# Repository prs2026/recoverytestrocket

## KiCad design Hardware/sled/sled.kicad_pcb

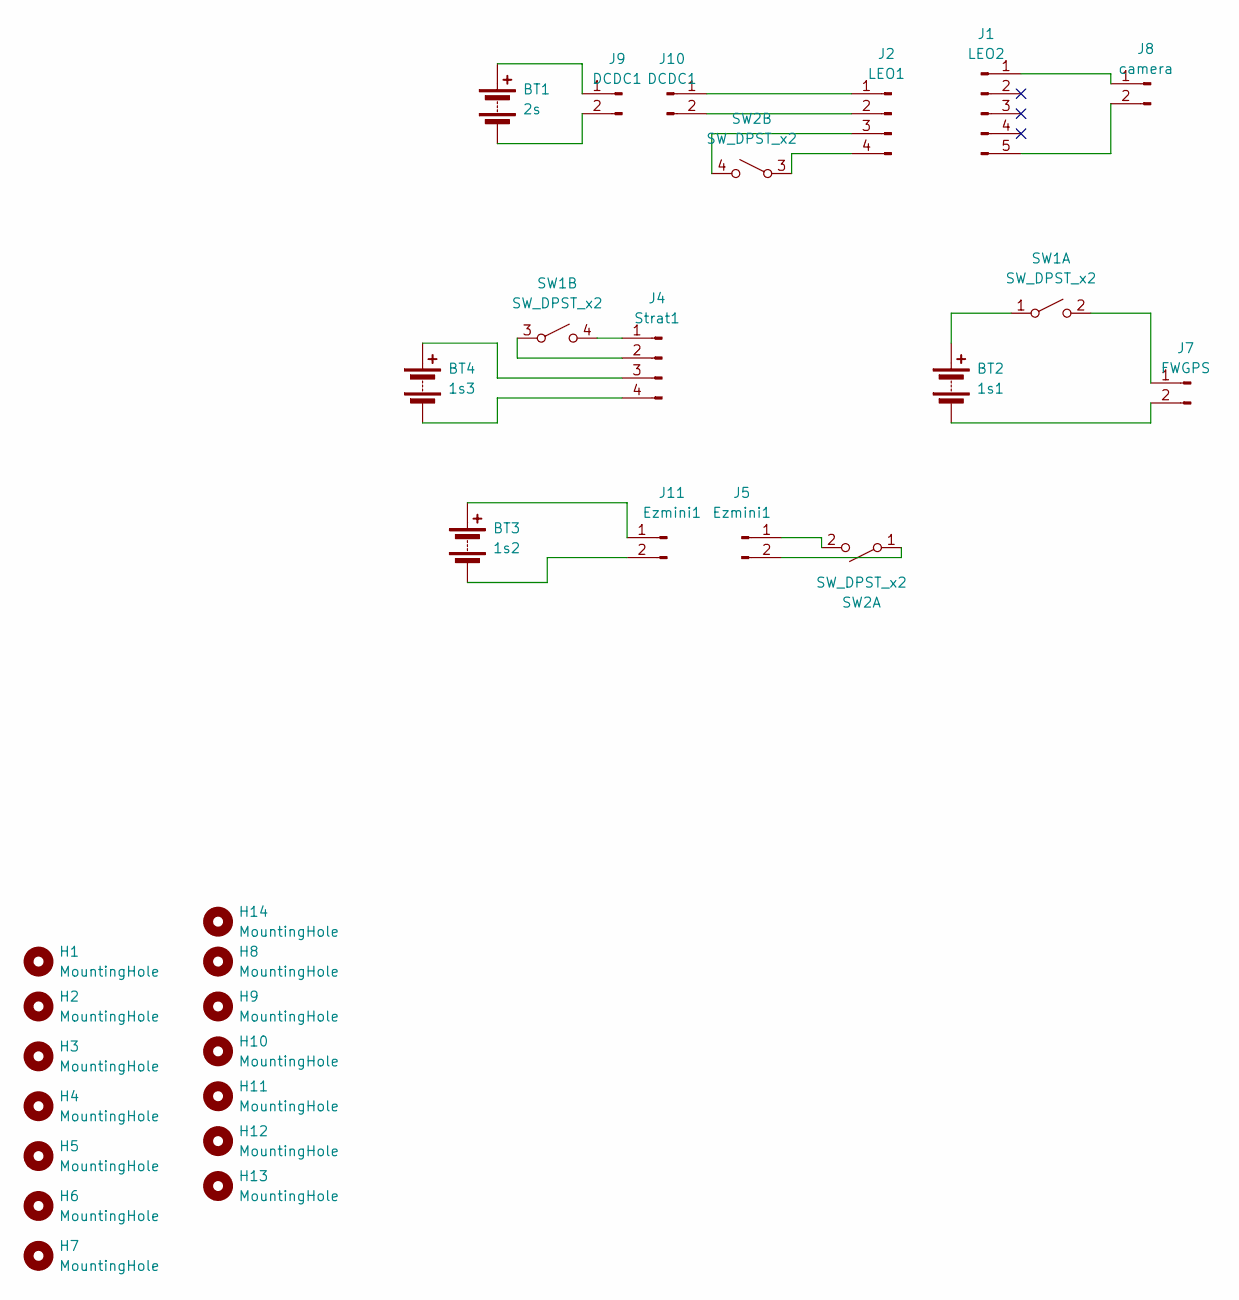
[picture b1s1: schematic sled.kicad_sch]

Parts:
BT1: 2s; PinHeader_1x02_P2.54mm_Vertical
BT2: 1s1; PinHeader_1x02_P2.54mm_Vertical
BT3: 1s2; PinHeader_1x02_P2.54mm_Vertical
BT4: 1s3; PinHeader_1x02_P2.54mm_Vertical
H1, H2, H3, H4: MountingHole; MountingHole_2.2mm_M2_DIN965_Pad
H5, H6, H7, H8, H9, H10, H11, H12, H13, H14: MountingHole; MountingHole_2.2mm_M3_DIN965_Pad_1
J1: LEO2; PinHeader_1x05_P2.54mm_Vertical
J2: LEO1; PinHeader_1x04_P2.54mm_Vertical
J4: Strat1; PinHeader_1x04_P3.08mm_Vertical
J5, J11: Ezmini1; PinHeader_1x02_P2.54mm_Vertical
J7: FWGPS; PinHeader_1x02_P2.54mm_Vertical
J8: camera; PinHeader_1x02_P2.54mm_Vertical
J9, J10: DCDC1; PinHeader_1x02_P2.54mm_Vertical
SW1, SW2: SW_DPST_x2; PinHeader_1x04_P2.54mm_Vertical

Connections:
unnamed: BT1.1 (+), J9.1
unnamed: BT1.2 (-), J9.2
unnamed: BT2.1 (+), SW1.1 (A)
unnamed: BT2.2 (-), J7.2
unnamed: BT3.1 (+), J11.1
unnamed: BT3.2 (-), J11.2
unnamed: BT4.1 (+), J4.3
unnamed: BT4.2 (-), J4.4
unnamed: J1.1, J8.1
unnamed: J1.5, J8.2
unnamed: J2.3, SW2.4 (B)
unnamed: J2.4, SW2.3 (A)
unnamed: J4.1, SW1.4 (B)
unnamed: J4.2, SW1.3 (A)
unnamed: J5.1, SW2.2 (B)
unnamed: J5.2, SW2.1 (A)
unnamed: J7.1, SW1.2 (B)
unnamed: J2.1, J10.1
unnamed: J2.2, J10.2

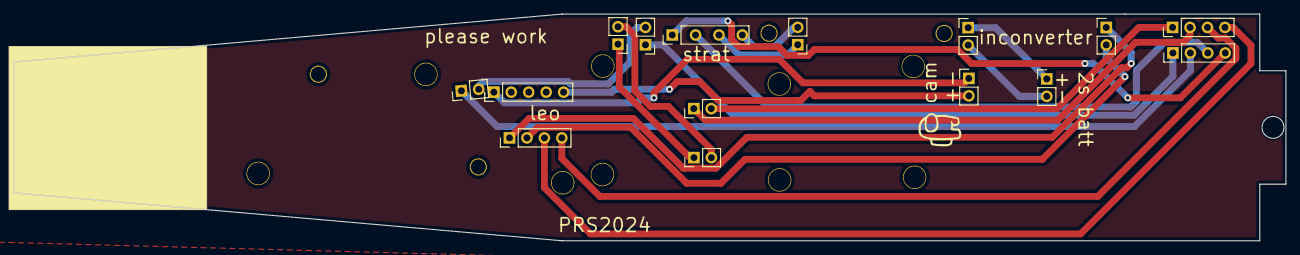
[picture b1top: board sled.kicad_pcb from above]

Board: 2 copper layers, 185.2 x 33.0 mm, 29 parts (0 on the bottom side), 19 nets.

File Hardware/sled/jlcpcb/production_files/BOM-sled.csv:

Comment,Designator,Footprint,LCSC
SW_DPST_x2,SW1,PinHeader_1x04_P2.54mm_Vertical,
Ezmini1,J11,PinHeader_1x02_P2.54mm_Vertical,
MountingHole,H7,MountingHole_2.2mm_M3_DIN965_Pad_1,
MountingHole,H14,MountingHole_2.2mm_M3_DIN965_Pad_1,
LEO1,J2,PinHeader_1x04_P2.54mm_Vertical,
LEO2,J1,PinHeader_1x05_P2.54mm_Vertical,
DCDC1,J10,PinHeader_1x02_P2.54mm_Vertical,
Ezmini1,J5,PinHeader_1x02_P2.54mm_Vertical,
MountingHole,H1,MountingHole_2.2mm_M2_DIN965_Pad,
MountingHole,H10,MountingHole_2.2mm_M3_DIN965_Pad_1,
1s2,BT3,PinHeader_1x02_P2.54mm_Vertical,
Strat1,J4,PinHeader_1x04_P3.08mm_Vertical,
2s,BT1,PinHeader_1x02_P2.54mm_Vertical,
DCDC1,J9,PinHeader_1x02_P2.54mm_Vertical,
MountingHole,H5,MountingHole_2.2mm_M3_DIN965_Pad_1,
1s1,BT2,PinHeader_1x02_P2.54mm_Vertical,
MountingHole,H9,MountingHole_2.2mm_M3_DIN965_Pad_1,
camera,J8,PinHeader_1x02_P2.54mm_Vertical,
MountingHole,H11,MountingHole_2.2mm_M3_DIN965_Pad_1,
MountingHole,H13,MountingHole_2.2mm_M3_DIN965_Pad_1,
MountingHole,H12,MountingHole_2.2mm_M3_DIN965_Pad_1,
SW_DPST_x2,SW2,PinHeader_1x04_P2.54mm_Vertical,
MountingHole,H2,MountingHole_2.2mm_M2_DIN965_Pad,
MountingHole,H8,MountingHole_2.2mm_M3_DIN965_Pad_1,
1s3,BT4,PinHeader_1x02_P2.54mm_Vertical,
MountingHole,H3,MountingHole_2.2mm_M2_DIN965_Pad,
MountingHole,H6,MountingHole_2.2mm_M3_DIN965_Pad_1,
MountingHole,H4,MountingHole_2.2mm_M2_DIN965_Pad,
FWGPS,J7,PinHeader_1x02_P2.54mm_Vertical,

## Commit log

2024-10-21 init
2024-10-21 cad work
2024-10-22 av bay work
2024-10-23 more work, av bay more exists now
2024-10-24 sled updates and charge cannons
2024-10-25 more av bay work
2024-10-26 more av bay work!
2024-10-28 work
2024-10-30 dv uploaf
2024-11-10 submin cad work
2024-11-11 bolted can
2024-11-25 more work
2024-12-03 hangoverinit
2024-12-24 new av bay cad
2024-12-28 yeah
2024-12-31 cone
2025-01-03 yeah.
    cam ded
2025-01-08 edited nosecone
2025-01-08 stashed
2025-01-13 avbayv3
2025-02-19 added things
2025-02-20 fixed it
2025-08-26 wierd
2025-12-03 stuff changed?
